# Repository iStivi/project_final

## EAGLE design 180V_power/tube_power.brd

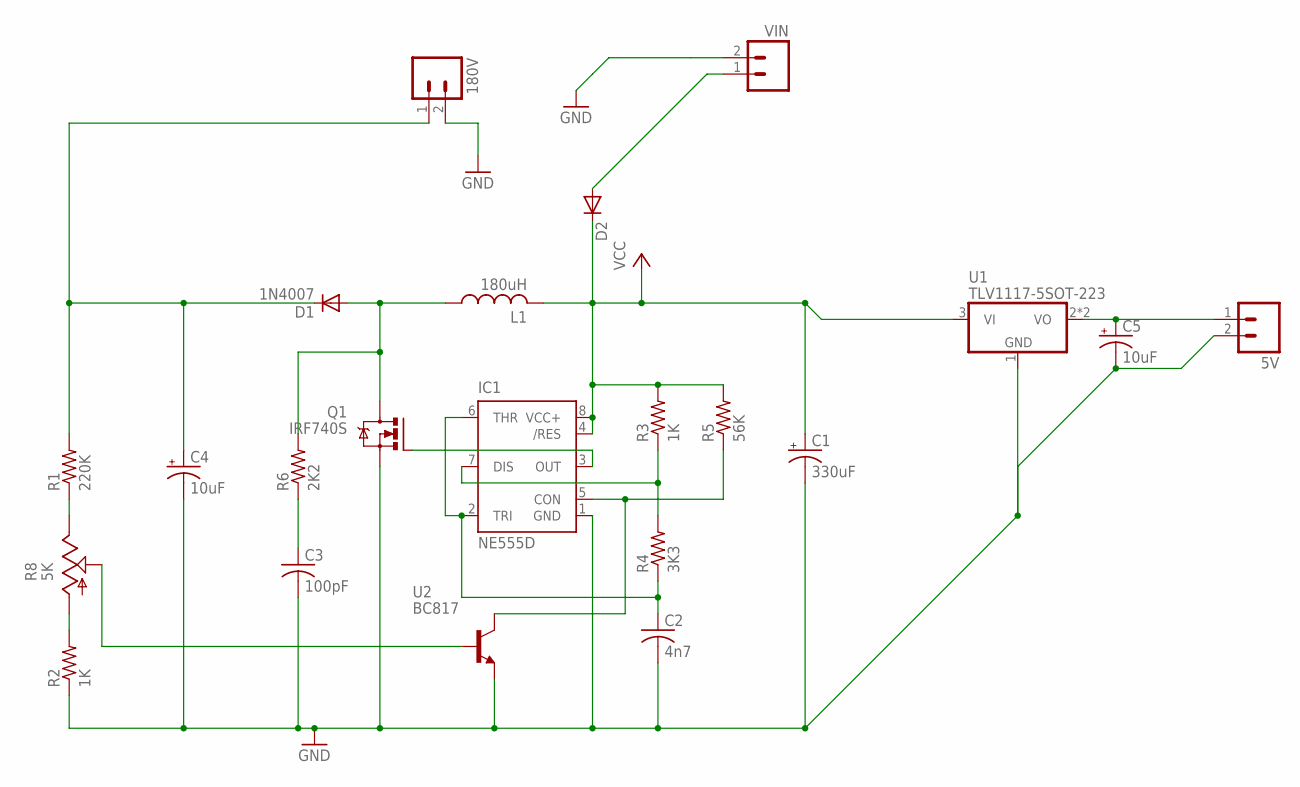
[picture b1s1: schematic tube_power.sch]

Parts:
5V, 180V: M023.5MM; SCREWTERMINAL-3.5MM-2
C1: 330uF; E5-10,5
C2: 4n7; C0805K
C3: 100pF; C0805K
C4: 10uF; E3,5-8
C5: 10uF; E2-5
D1: 1N4007; SMA-DIODE
D2: DIODESOD-80; SOD80C
IC1: NE555D; SO08
L1: 180uH; RBL0712
Q1: IRF740S; TO263
R1: 220K; 0207/10
R2: 1K; R1206
R3: 1K; R0805
R4: 3K3; R0805
R5: 56K; R0805
R6: 2K2; R0805
R8: 5K; TRIM-EVM2N
U1: TLV1117-5SOT-223; SOT-223
U2: BC817; SOT-23
VIN: M023.5MM; SCREWTERMINAL-3.5MM-2

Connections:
5V: 5V.1, C5.+, U1.2 (VO), U1.4 (VO)
180V: 180V.1, C4.+, D1.C, R1.2
CON: IC1.5 (CON), R5.1, U2.3 (C)
DIS: IC1.7 (DIS), R3.1, R4.2
GND: 5V.2, 180V.2, C1.-, C2.2, C3.2, C4.-, C5.-, IC1.1 (GND), Q1.2 (S), R2.1, U1.1 (GND), U2.2 (E), VIN.2
L1: D1.A, L1.P$1 (1), Q1.3 (D), R6.2
unnamed: R8.P$2 (S), U2.1 (B)
unnamed: D2.A, VIN.1
unnamed: R2.2, R8.P$1 (A)
OUT: IC1.3 (OUT), Q1.1 (G)
R1: R1.1, R8.P$3 (E)
R6: C3.1, R6.1
THR: C2.1, IC1.2 (TRI), IC1.6 (THR), R4.1
VCC: C1.+, D2.C, IC1.4 (/RES), IC1.8 (VCC+), L1.P$2 (2), R3.2, R5.2, U1.3 (VI)

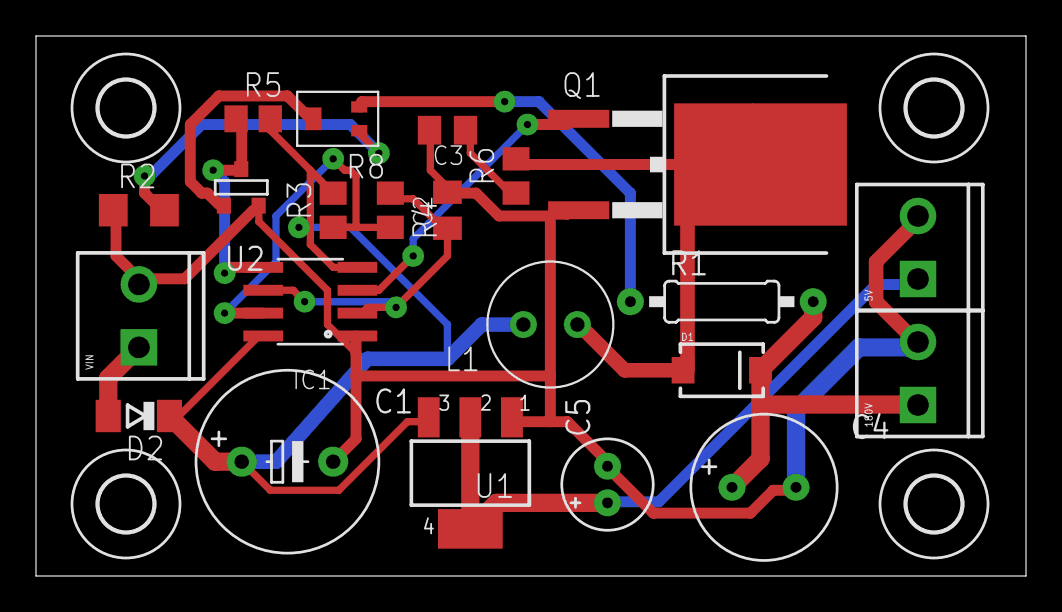
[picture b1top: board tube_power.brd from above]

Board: 2 copper layers, 55.0 x 30.0 mm, 28 parts (1 on the bottom side), 14 nets.

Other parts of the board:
U$1, U$2, U$4, U$5: 3,0-SMALL
U$3: BUZZBOY-SILK
U$6: BUZZBOY

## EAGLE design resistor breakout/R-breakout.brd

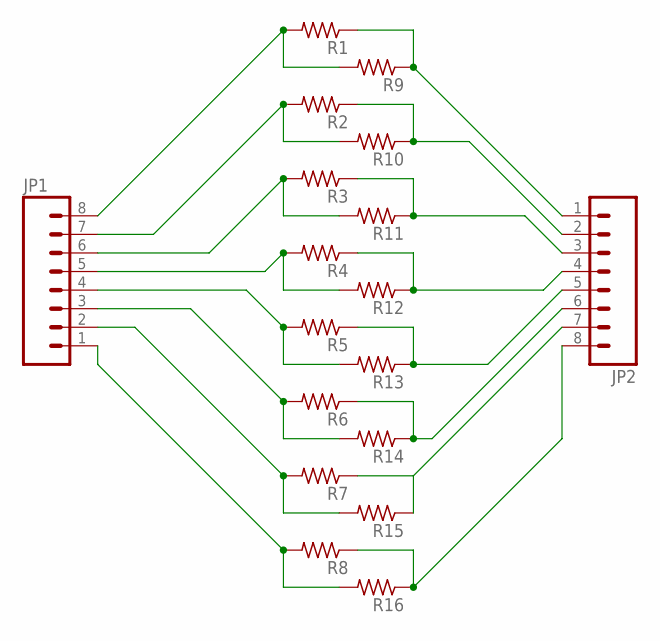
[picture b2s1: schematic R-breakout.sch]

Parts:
JP1, JP2: M081X08; 1X08
R1, R2, R3, R4, R5, R6, R7, R8: RESISTORR0805; R0805
R9, R10, R11, R12, R13, R14, R15, R16: RESISTORR1206; R1206

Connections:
unnamed: JP1.8, R1.2, R9.2
unnamed: JP1.7, R2.2, R10.2
unnamed: JP1.6, R3.2, R11.2
unnamed: JP1.5, R4.2, R12.2
unnamed: JP1.4, R5.2, R13.2
unnamed: JP1.3, R6.2, R14.2
unnamed: JP1.2, R7.2, R15.2
unnamed: JP1.1, R8.2, R16.2
unnamed: JP2.1, R1.1, R9.1
unnamed: JP2.2, R2.1, R10.1
unnamed: JP2.3, R3.1, R11.1
unnamed: JP2.4, R4.1, R12.1
unnamed: JP2.5, R5.1, R13.1
unnamed: JP2.6, R6.1, R14.1
unnamed: JP2.7, R7.1, R15.1
unnamed: JP2.8, R8.1, R16.1

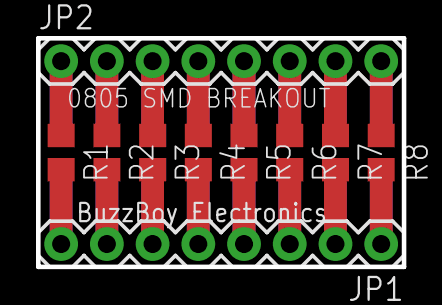
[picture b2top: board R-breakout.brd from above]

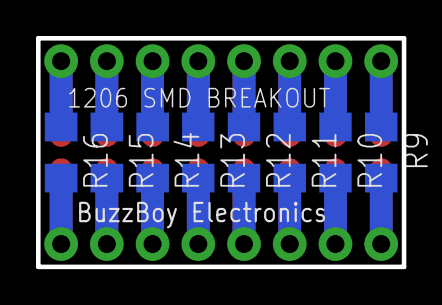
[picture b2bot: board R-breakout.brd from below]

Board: 2 copper layers, 20.3 x 12.7 mm, 18 parts (8 on the bottom side), 16 nets.

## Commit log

2014-10-23 :octocat: Added .gitattributes & .gitignore files
2014-10-23 first commit
2014-12-01 fixed document info
2014-12-22 2 new breakout boards
2014-12-22 change
2015-08-07 new 180V board design
2015-08-26 added diode and resistor to 180V power
2015-08-31 new boards printed
2015-09-20 update document data
